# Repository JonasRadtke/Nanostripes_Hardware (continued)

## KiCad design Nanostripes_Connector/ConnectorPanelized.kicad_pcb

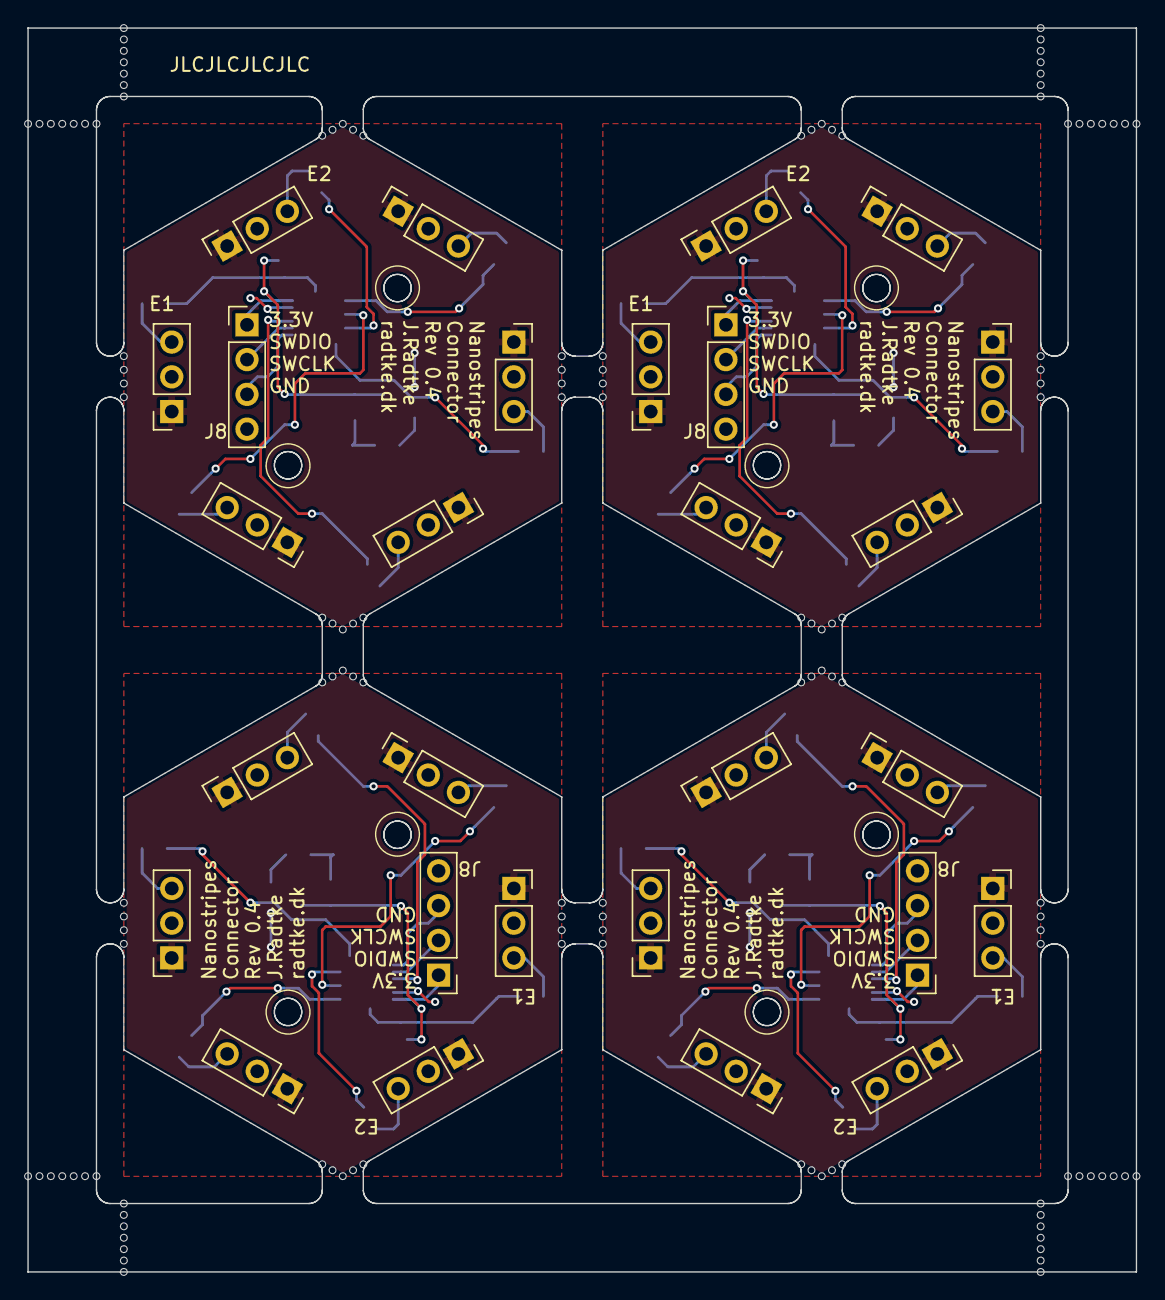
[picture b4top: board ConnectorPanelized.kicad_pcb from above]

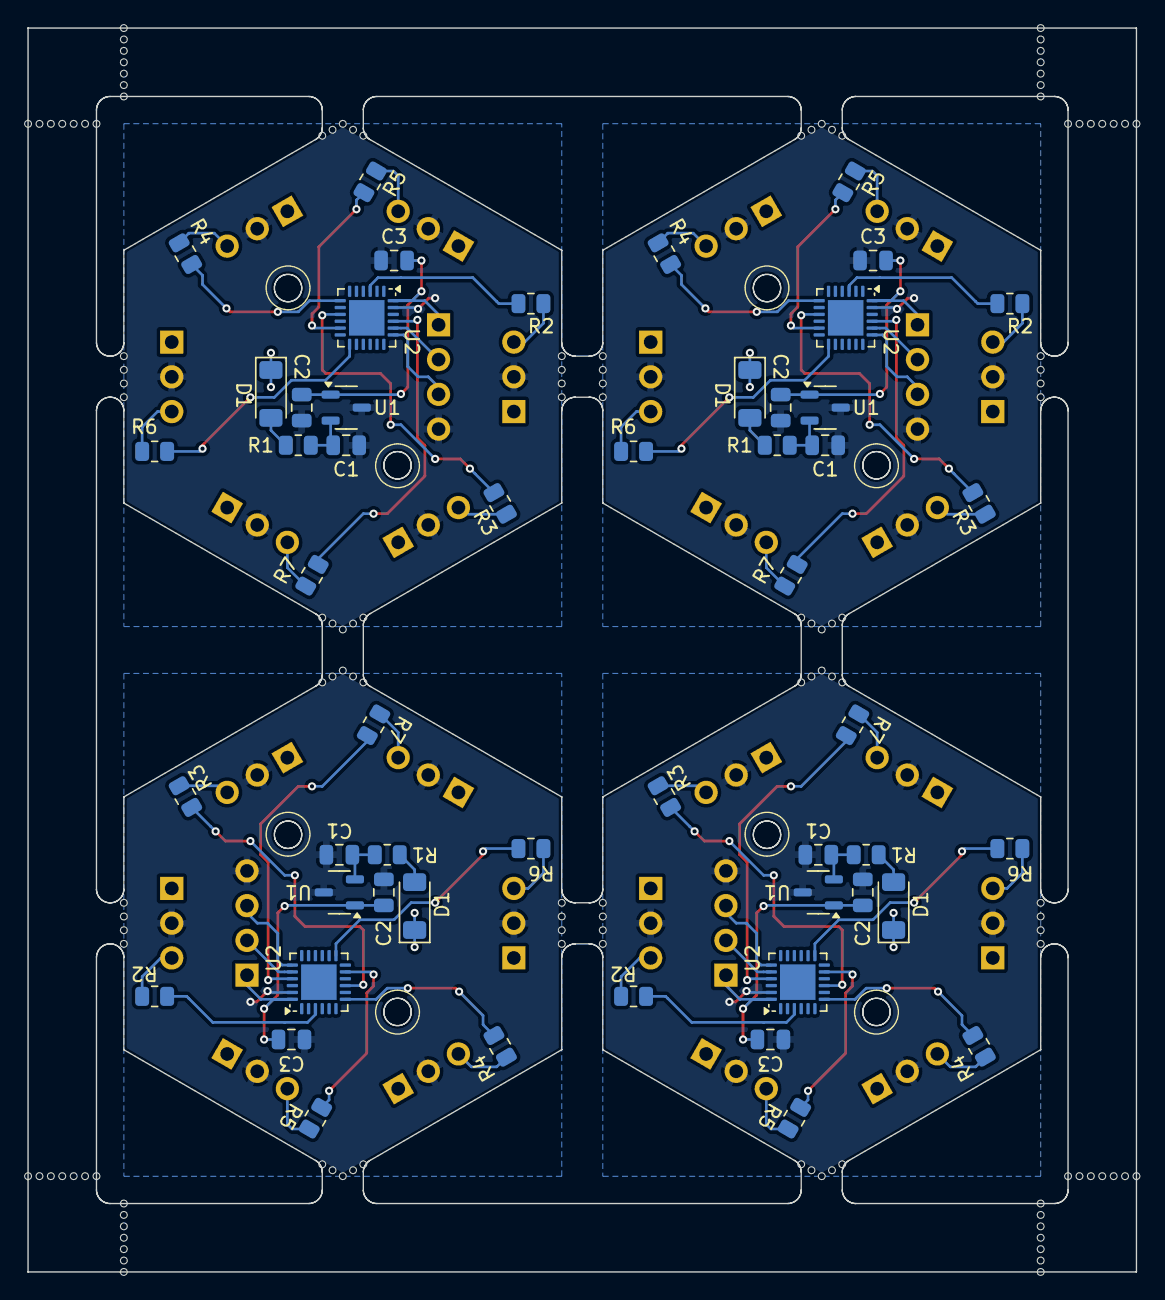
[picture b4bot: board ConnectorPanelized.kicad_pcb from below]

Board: 2 copper layers, 81.0 x 90.9 mm, 208 parts (52 on the bottom side), 76 nets.

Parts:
C1, C1#2, C1#3, C1#4: 1u; C_0805_2012Metric
C2, C2#2, C2#3, C2#4: 0,47u; C_0805_2012Metric
C3, C3#2, C3#3, C3#4: 100n; C_0805_2012Metric
D1, D1#2, D1#3, D1#4: 24V; D_MiniMELF
J1, J1#2, J1#3, J1#4: Input_E1; PinSocket_1x03_P2.54mm_Vertical
J2, J2#2, J2#3, J2#4: Input_E2; PinSocket_1x03_P2.54mm_Vertical
J3, J3#2, J3#3, J3#4: Input_E3; PinSocket_1x03_P2.54mm_Vertical
J4, J4#2, J4#3, J4#4: Input_E4; PinSocket_1x03_P2.54mm_Vertical
J5, J5#2, J5#3, J5#4: Input_E5; PinSocket_1x03_P2.54mm_Vertical
J6, J6#2, J6#3, J6#4: Input_E6; PinSocket_1x03_P2.54mm_Vertical
J8, J8#2, J8#3, J8#4: Conn_01x04_Pin; PinHeader_1x04_P2.54mm_Vertical
KiKit_MB_1_1, KiKit_MB_1_2, KiKit_MB_1_3, KiKit_MB_1_4, KiKit_MB_2_1, KiKit_MB_2_2, KiKit_MB_2_3, KiKit_MB_2_4, KiKit_MB_3_1, KiKit_MB_3_2, KiKit_MB_3_3, KiKit_MB_3_4, KiKit_MB_3_5, KiKit_MB_4_1, KiKit_MB_4_2, KiKit_MB_4_3, KiKit_MB_4_4, KiKit_MB_4_5, KiKit_MB_5_1, KiKit_MB_5_2, KiKit_MB_5_3, KiKit_MB_5_4, KiKit_MB_6_1, KiKit_MB_6_2, KiKit_MB_6_3, KiKit_MB_6_4, KiKit_MB_7_1, KiKit_MB_7_2, KiKit_MB_7_3, KiKit_MB_7_4, KiKit_MB_7_5, KiKit_MB_8_1, KiKit_MB_8_2, KiKit_MB_8_3, KiKit_MB_8_4, KiKit_MB_8_5, KiKit_MB_9_1, KiKit_MB_9_2, KiKit_MB_9_3, KiKit_MB_9_4, KiKit_MB_10_1, KiKit_MB_10_2, KiKit_MB_10_3, KiKit_MB_10_4, KiKit_MB_11_1, KiKit_MB_11_2, KiKit_MB_11_3, KiKit_MB_11_4, KiKit_MB_11_5, KiKit_MB_12_1, KiKit_MB_12_2, KiKit_MB_12_3, KiKit_MB_12_4, KiKit_MB_12_5, KiKit_MB_13_1, KiKit_MB_13_2, KiKit_MB_13_3, KiKit_MB_13_4, KiKit_MB_14_1, KiKit_MB_14_2, KiKit_MB_14_3, KiKit_MB_14_4, KiKit_MB_15_1, KiKit_MB_15_2, KiKit_MB_15_3, KiKit_MB_15_4, KiKit_MB_15_5, KiKit_MB_16_1, KiKit_MB_16_2, KiKit_MB_16_3, KiKit_MB_16_4, KiKit_MB_16_5, KiKit_MB_17_1, KiKit_MB_17_2, KiKit_MB_17_3, KiKit_MB_17_4, KiKit_MB_17_5, KiKit_MB_17_6, KiKit_MB_17_7, KiKit_MB_18_1, KiKit_MB_18_2, KiKit_MB_18_3, KiKit_MB_18_4, KiKit_MB_18_5, KiKit_MB_18_6, KiKit_MB_18_7, KiKit_MB_19_1, KiKit_MB_19_2, KiKit_MB_19_3, KiKit_MB_19_4, KiKit_MB_19_5, KiKit_MB_19_6, KiKit_MB_19_7, KiKit_MB_20_1, KiKit_MB_20_2, KiKit_MB_20_3, KiKit_MB_20_4, KiKit_MB_20_5, KiKit_MB_20_6, KiKit_MB_20_7, KiKit_MB_21_1, KiKit_MB_21_2, KiKit_MB_21_3, KiKit_MB_21_4, KiKit_MB_21_5, KiKit_MB_21_6, KiKit_MB_21_7, KiKit_MB_22_1, KiKit_MB_22_2, KiKit_MB_22_3, KiKit_MB_22_4, KiKit_MB_22_5, KiKit_MB_22_6, KiKit_MB_22_7, KiKit_MB_23_1, KiKit_MB_23_2, KiKit_MB_23_3, KiKit_MB_23_4, KiKit_MB_23_5, KiKit_MB_23_6, KiKit_MB_23_7, KiKit_MB_24_1, KiKit_MB_24_2, KiKit_MB_24_3, KiKit_MB_24_4, KiKit_MB_24_5, KiKit_MB_24_6, KiKit_MB_24_7: NPTH
R1, R1#2, R1#3, R1#4: 120; R_0805_2012Metric
R2, R2#2, R2#3, R2#4, R3, R3#2, R3#3, R3#4, R4, R4#2, R4#3, R4#4, R5, R5#2, R5#3, R5#4, R6, R6#2, R6#3, R6#4, R7, R7#2, R7#3, R7#4: 2.2k; R_0805_2012Metric
U1, U1#2, U1#3, U1#4: 78L03; SOT-23-3
U2, U2#2, U2#3, U2#4: ATSAMD11D14A-M; QFN-24-1EP_4x4mm_P0.5mm_EP2.6x2.6mm

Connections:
Board_0-+3.3V: C2#4.1, C3.1, J8.1, U1#4.1 (VOUT), U2.24 (VDD)
Board_0-+42V: D1.1 (K), J1.1, J2#2.1, J3#3.1, J4.1, J5#4.1, J6#4.1
Board_0-/Controller/E1: J1.3, R2#3.2
Board_0-/Controller/E2: J2#2.3, R5#3.2
Board_0-/Controller/E3: J3#3.3, R4#3.2
Board_0-/Controller/E4: J4.3, R6#4.2
Board_0-/Controller/E5: J5#4.3, R3#3.2
Board_0-/Controller/E6: J6#4.3, R7.2
Board_0-GND: C1#2.2, C2#4.2, C3.2, J1.2, J2#2.2, J3#3.2, J4.2, J5#4.2, J6#4.2, J8.4, U1#4.3 (GND), U2.23 (GND)
Board_0-Net-(D1-A): D1.2 (A), R1#3.1
Board_0-Net-(U1-IN): C1#2.1, R1#3.2, U1#4.2 (IN)
Board_0-Net-(U2-PA04): R2#3.1, U2.3 (PA04)
Board_0-Net-(U2-PA08/XIN): R4#3.1, U2.7 (PA08/XIN)
Board_0-Net-(U2-PA10): R3#3.1, U2.9 (PA10)
Board_0-Net-(U2-PA14): R5#3.1, U2.11 (PA14)
Board_0-Net-(U2-PA16): R6#4.1, U2.13 (PA16)
Board_0-Net-(U2-PA24): R7.1, U2.21 (PA24)
Board_0-SWCLK: J8.3, U2.19 (PA30/SWCLK)
Board_0-SWDIO: J8.2, U2.20 (PA31/SWDIO)
Board_1-+3.3V: C2#2.1, C3#3.1, J8#2.1, U1#3.1 (VOUT), U2#2.24 (VDD)
Board_1-+42V: D1#4.1 (K), J1#3.1, J2#4.1, J3#4.1, J4#2.1, J5#3.1, J6.1
Board_1-/Controller/E1: J1#3.3, R2#2.2
Board_1-/Controller/E2: J2#4.3, R5#2.2
Board_1-/Controller/E3: J3#4.3, R4#2.2
Board_1-/Controller/E4: J4#2.3, R6#3.2
Board_1-/Controller/E5: J5#3.3, R3#2.2
Board_1-/Controller/E6: J6.3, R7#4.2
Board_1-GND: C1#3.2, C2#2.2, C3#3.2, J1#3.2, J2#4.2, J3#4.2, J4#2.2, J5#3.2, J6.2, J8#2.4, U1#3.3 (GND), U2#2.23 (GND)
Board_1-Net-(D1-A): D1#4.2 (A), R1.1
Board_1-Net-(U1-IN): C1#3.1, R1.2, U1#3.2 (IN)
Board_1-Net-(U2-PA04): R2#2.1, U2#2.3 (PA04)
Board_1-Net-(U2-PA08/XIN): R4#2.1, U2#2.7 (PA08/XIN)
Board_1-Net-(U2-PA10): R3#2.1, U2#2.9 (PA10)
Board_1-Net-(U2-PA14): R5#2.1, U2#2.11 (PA14)
Board_1-Net-(U2-PA16): R6#3.1, U2#2.13 (PA16)
Board_1-Net-(U2-PA24): R7#4.1, U2#2.21 (PA24)
Board_1-SWCLK: J8#2.3, U2#2.19 (PA30/SWCLK)
Board_1-SWDIO: J8#2.2, U2#2.20 (PA31/SWDIO)
Board_2-+3.3V: C2#3.1, C3#2.1, J8#3.1, U1.1 (VOUT), U2#3.24 (VDD)
Board_2-+42V: D1#2.1 (K), J1#4.1, J2#3.1, J3#2.1, J4#4.1, J5#2.1, J6#3.1
Board_2-/Controller/E1: J1#4.3, R2.2
Board_2-/Controller/E2: J2#3.3, R5#4.2
Board_2-/Controller/E3: J3#2.3, R4#4.2
Board_2-/Controller/E4: J4#4.3, R6.2
Board_2-/Controller/E5: J5#2.3, R3#4.2
Board_2-/Controller/E6: J6#3.3, R7#2.2
Board_2-GND: C1#4.2, C2#3.2, C3#2.2, J1#4.2, J2#3.2, J3#2.2, J4#4.2, J5#2.2, J6#3.2, J8#3.4, U1.3 (GND), U2#3.23 (GND)
Board_2-Net-(D1-A): D1#2.2 (A), R1#4.1
Board_2-Net-(U1-IN): C1#4.1, R1#4.2, U1.2 (IN)
Board_2-Net-(U2-PA04): R2.1, U2#3.3 (PA04)
Board_2-Net-(U2-PA08/XIN): R4#4.1, U2#3.7 (PA08/XIN)
Board_2-Net-(U2-PA10): R3#4.1, U2#3.9 (PA10)
Board_2-Net-(U2-PA14): R5#4.1, U2#3.11 (PA14)
Board_2-Net-(U2-PA16): R6.1, U2#3.13 (PA16)
Board_2-Net-(U2-PA24): R7#2.1, U2#3.21 (PA24)
Board_2-SWCLK: J8#3.3, U2#3.19 (PA30/SWCLK)
Board_2-SWDIO: J8#3.2, U2#3.20 (PA31/SWDIO)
Board_3-+3.3V: C2.1, C3#4.1, J8#4.1, U1#2.1 (VOUT), U2#4.24 (VDD)
Board_3-+42V: D1#3.1 (K), J1#2.1, J2.1, J3.1, J4#3.1, J5.1, J6#2.1
Board_3-/Controller/E1: J1#2.3, R2#4.2
Board_3-/Controller/E2: J2.3, R5.2
Board_3-/Controller/E3: J3.3, R4.2
Board_3-/Controller/E4: J4#3.3, R6#2.2
Board_3-/Controller/E5: J5.3, R3.2
Board_3-/Controller/E6: J6#2.3, R7#3.2
Board_3-GND: C1.2, C2.2, C3#4.2, J1#2.2, J2.2, J3.2, J4#3.2, J5.2, J6#2.2, J8#4.4, U1#2.3 (GND), U2#4.23 (GND)
Board_3-Net-(D1-A): D1#3.2 (A), R1#2.1
Board_3-Net-(U1-IN): C1.1, R1#2.2, U1#2.2 (IN)
Board_3-Net-(U2-PA04): R2#4.1, U2#4.3 (PA04)
Board_3-Net-(U2-PA08/XIN): R4.1, U2#4.7 (PA08/XIN)
Board_3-Net-(U2-PA10): R3.1, U2#4.9 (PA10)
Board_3-Net-(U2-PA14): R5.1, U2#4.11 (PA14)
Board_3-Net-(U2-PA16): R6#2.1, U2#4.13 (PA16)
Board_3-Net-(U2-PA24): R7#3.1, U2#4.21 (PA24)
Board_3-SWCLK: J8#4.3, U2#4.19 (PA30/SWCLK)
Board_3-SWDIO: J8#4.2, U2#4.20 (PA31/SWDIO)

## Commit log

2025-01-05 Rev0.4
2025-01-06 all hardware in one repo
2025-01-06 update values
2025-01-10 finished and panelized
2025-01-11 readme
2025-02-14 updated component values
